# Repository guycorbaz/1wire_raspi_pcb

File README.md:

# 1-Wire Raspberry Pi Adapter

A KiCad project for a simple interface board connecting 1-Wire sensors to a Raspberry Pi.

This hardware is part of the [boilert](https://github.com/guycorbaz/boilert) project, which monitors boiler temperatures using a Raspberry Pi.

## Features

- **Raspberry Pi Integration**: Designed for the standard 40-pin Raspberry Pi GPIO header.
- **1-Wire Connectivity**: Includes Molex Micro-Fit 3.0 connectors for 1-Wire sensors and external power.
- **Integrated Bus Support**: Schematic includes the necessary pull-up resistor and power filtering.

## Project Information

- **Title**: 1-Wire Raspi
- **Creator**: Guy Corbaz
- **Revision**: 1
- **Date**: 15 Nov 2012 (Legacy) / Updated 2025

---
*Created using KiCad 9.0*

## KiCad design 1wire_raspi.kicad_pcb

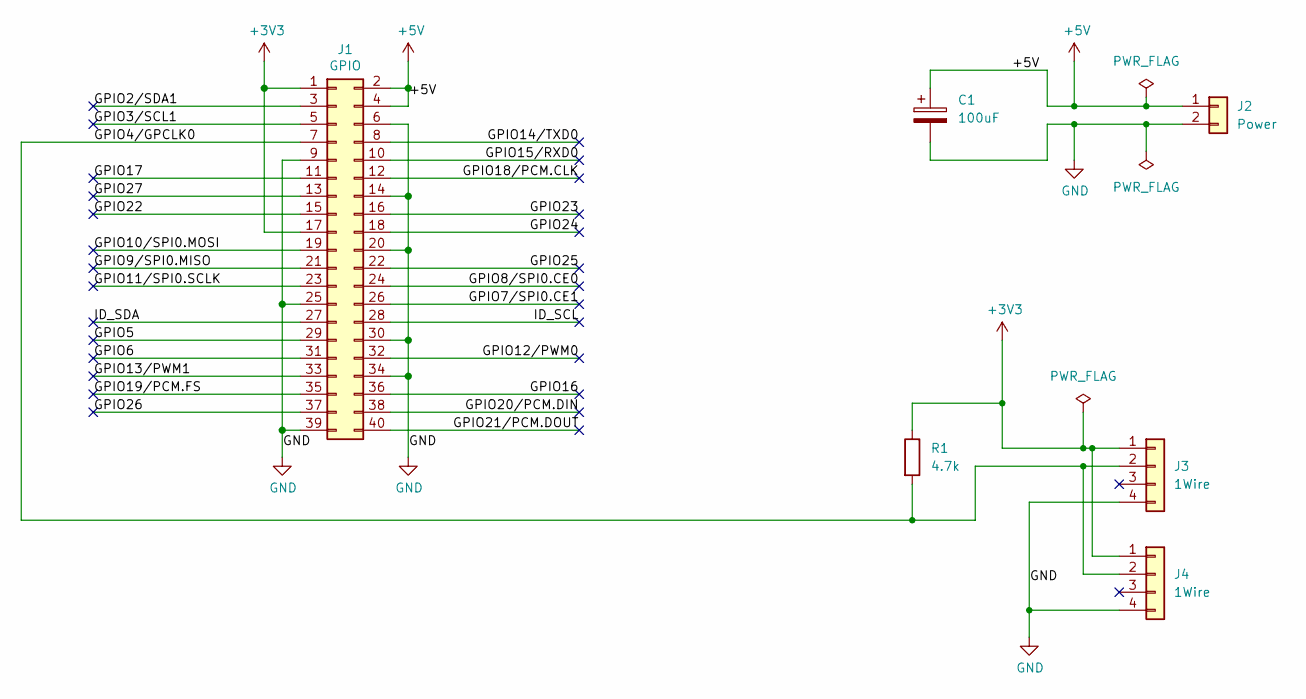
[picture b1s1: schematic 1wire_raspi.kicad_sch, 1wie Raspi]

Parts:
C1: 100uF; CP_Radial_D5.0mm_P2.00mm
J1: GPIO; PinSocket_2x20_P2.54mm_Vertical
J2: Power; Molex_Micro-Fit_3.0_43045-0212_2x01_P3.00mm_Vertical
J3, J4: 1Wire; Molex_Micro-Fit_3.0_43045-0412_2x02_P3.00mm_Vertical
R1: 4.7k; R_Axial_DIN0204_L3.6mm_D1.6mm_P7.62mm_Horizontal

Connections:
+3V3: J1.1, J1.17, J3.1, J4.1, R1.1
+5V: C1.1, J1.2, J1.4, J2.1
/GPIO2/SDA1: J1.3
/GPIO3/SCL1: J1.5
/GPIO4/GPCLK0: J1.7, J3.2, J4.2, R1.2
/GPIO5: J1.29
/GPIO6: J1.31
/GPIO7/SPI0.CE1: J1.26
/GPIO8/SPI0.CE0: J1.24
/GPIO9/SPI0.MISO: J1.21
/GPIO10/SPI0.MOSI: J1.19
/GPIO11/SPI0.SCLK: J1.23
/GPIO12/PWM0: J1.32
/GPIO13/PWM1: J1.33
/GPIO14/TXD0: J1.8
/GPIO15/RXD0: J1.10
/GPIO16: J1.36
/GPIO17: J1.11
/GPIO18/PCM.CLK: J1.12
/GPIO19/PCM.FS: J1.35
/GPIO20/PCM.DIN: J1.38
/GPIO21/PCM.DOUT: J1.40
/GPIO22: J1.15
/GPIO23: J1.16
/GPIO24: J1.18
/GPIO25: J1.22
/GPIO26: J1.37
/GPIO27: J1.13
/ID_SCL: J1.28
/ID_SDA: J1.27
GND: C1.2, J1.6, J1.9, J1.14, J1.20, J1.25, J1.30, J1.34, J1.39, J2.2, J3.4, J4.4

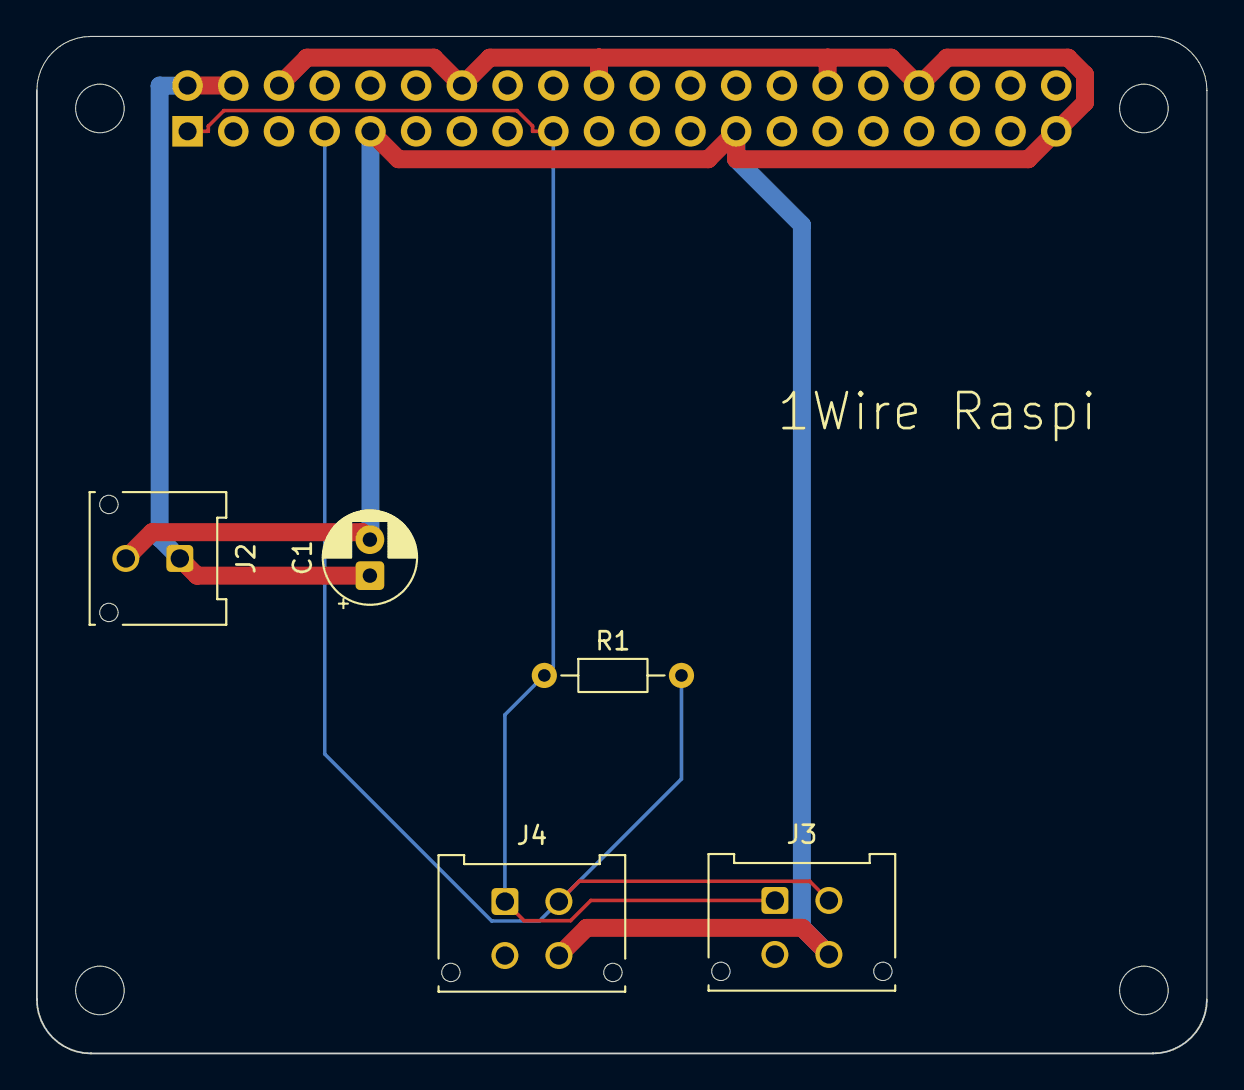
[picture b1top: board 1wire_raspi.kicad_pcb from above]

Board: 2 copper layers, 65.0 x 56.5 mm, 10 parts (1 on the bottom side), 4 nets.

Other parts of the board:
MH1, MH2, MH3, MH4: MountingHole_2.7mm_M2.5

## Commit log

2025-12-22 Initial version
2026-01-09 Corrected page size
